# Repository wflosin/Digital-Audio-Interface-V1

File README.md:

This is a complete design for a digital audio interface. The features include:
- 1/4" jack input (mono)
- Headphone output (loobpack or computer audio output)
- Active tone control, three knobs (bass, mid, treble) 
- Active volume control
- Clipping indicator
- HID buttons (mute, volume up, volume down)
- Entirely USB-powered
- No screws needed, the panel snap fits into the enclosure

What is found in this repository:
- Schematic and Board files (Eagle CAD)
- Images of the schematic and board
- Parts list, and Digikey order
- Gerber files
- 3D models for the enclosure, and potentiometer and button caps

The circuit uses the audio codex PCM2906 from TI, which includes a USB interface. Although many of the parts can be hand-soldered, it is recoommended to reflow solder the board. 

The overall cost of parts and printing was approximately $115 CAD (Oct-2025). Parts were selected to minimize noise thorughout the circuit, and so cheaper alternatives could be used instead. 
Parts were ordered through Digikey and from Texas Instruments. The enclosure was 3D printed, but a metal enclosure could probe useful for shielding. 

Notable issues to be improved on in the next iteration: 
- Headphone pop when plugging in
- When the bass tone control is turned up too high, all sound cuts out
- When listening through headphones on the loobback setting, the only way to control the headphone volume is with the gain knob. This should have a separate volume control. 

Noise and performance metrics of the board were not evaluated once completed. Audio quality was sufficient for this iteration, but naturally, performance metrics are a must potentially commercializable devices. 

I hope you like it!

Below are several sources that helped in the creation of this design:
- https://www.theseus.fi/bitstream/handle/10024/857714/Heikkinen_Tuomas-Pyry.pdf
- https://kastner.ucsd.edu/ryan/wp-content/uploads/sites/5/2022/06/admin/usb-audio-interface.pdf
- https://guitarnuts2.proboards.com/thread/7842/modeling-electric-guitar-ltspice
- https://circuitdigest.com/electronic-circuits/audio-equalizer-tone-control-circuit-with-bass-treble-and-mid-frequency-control
- https://www.ti.com/lit/ug/tidu034/tidu034.pdf
- Small Signal Audio Design, by Douglas Self (chapter 9)
- https://www.edn.com/signal-distortion-from-high-k-ceramic-capacitors/

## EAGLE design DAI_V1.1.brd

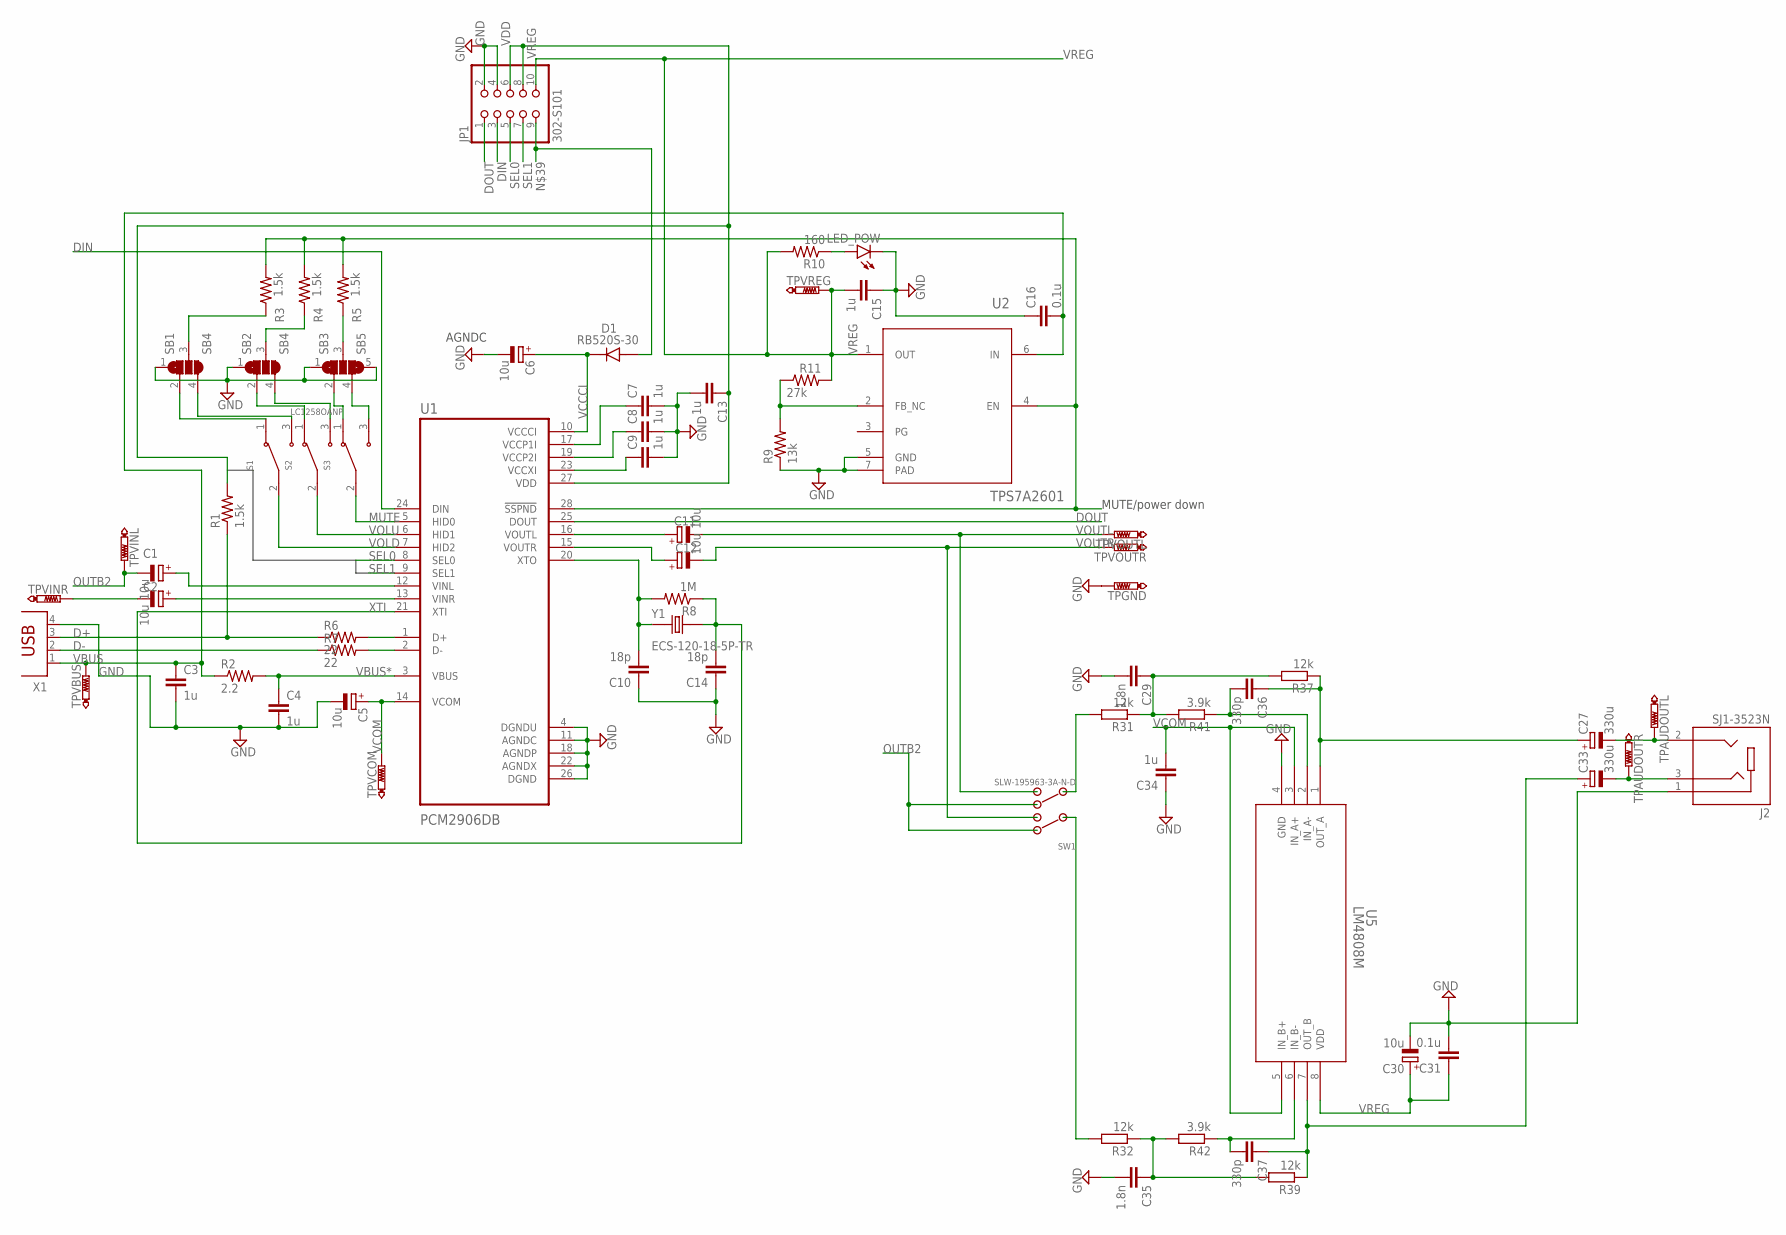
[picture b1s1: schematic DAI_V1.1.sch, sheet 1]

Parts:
C1, C2, C11, C12: 10u; PANASONIC_D
C3, C4, C7, C8, C9, C13, C15, C34: 1u; C0805
C5, C6, C30: 10u; PANASONIC_B
C10, C14: 18p; C0805
C16, C31: 0.1u; C0805
C27, C33: 330u; E3,5-10
C29, C35: 1.8n; C1206
C36, C37: 330p; C1206
D1: RB520S-30; DIO_RB520S-30
J2: SJ1-3523N; CUI_SJ1-3523N
JP1: 302-S101; 2X05
LED_POW: LED5MM
R1, R3, R4, R5: 1.5k; R0805
R2: 2.2; R0805
R6, R7: 22; R0805
R8: 1M; R0805
R9: 13k; R0805
R10: 160; R0805
R11: 27k; R0805
R31, R32, R37, R39: 12k; M1206
R41, R42: 3.9k; M1206
S1, S3: LC1258EENP; SW_LC1258EENP
S2: LC1258OANP; SW_LC1258EENP
SB1, SB2: SB4
SB3: SB5
SW1: SLW-195963-3A-N-D; SW-T3-4B-A-A3-S2
TPAUDOUTL: PTR1PAD1-13; P1-13
TPAUDOUTR: PTR1PAD1-13; P1-13
TPGND: PTR1PAD1-13; P1-13
TPVBUS: PTR1PAD1-13; P1-13
TPVCOM: PTR1PAD1-13; P1-13
TPVINL: PTR1PAD1-13; P1-13
TPVINR: PTR1PAD1-13; P1-13
TPVOUTL: PTR1PAD1-13; P1-13
TPVOUTR: PTR1PAD1-13; P1-13
TPVREG: PTR1PAD1-13; P1-13
U1: PCM2906DB; SOP65P780X200-28N
U2: TPS7A2601; DRV0006A_NV
U5: LM4808M; M08A
X1: PN61729
Y1: ECS-120-18-5P-TR; XTAL_ECS-120-18-5P-TR

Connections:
AUDOUTL: C27.-, J2.2, TPAUDOUTL.TP
AUDOUTR: C33.-, J2.3, TPAUDOUTR.TP
D+: R1.1, R6.1, X1.3
D-: R7.1, X1.2
DIN: JP1.3, U1.24 (DIN)
DOUT: JP1.1, U1.25 (DOUT)
GND: C3.2, C4.2, C5.-, C6.-, C7.2, C8.2, C9.2, C10.1, C13.2, C14.1, C15.1, C16.1, C29.2, C30.-, C31.2, C34.1, C35.2, J2.1, JP1.2, JP1.4, LED_POW.K (C), R9.1, SB1.1, SB2.1, SB3.1, SB3.5, TPGND.TP, U1.4 (DGNDU), U1.11 (AGNDC), U1.18 (AGNDP), U1.22 (AGNDX), U1.26 (DGND), U2.5 (GND), U2.7 (PAD), U5.4 (GND), X1.4; also elsewhere on the board
MUTE: S3.2 (COM), U1.5 (HID0)
unnamed: R6.2, U1.1 (D+)
unnamed: R7.2, U1.2 (D-)
unnamed: R32.2, SW1.2
unnamed: R3.1, SB1.3
unnamed: C29.1, R31.1, R37.2, R41.2
unnamed: R5.1, SB3.3
unnamed: LED_POW.A, R10.1
unnamed: C35.1, R32.1, R39.2, R42.2
unnamed: C33.+, C37.1, R39.1, U5.7 (OUT_B)
unnamed: R4.1, SB2.3
unnamed: S1.1 (NC), SB1.2
unnamed: R9.2, R11.1, U2.2 (FB_NC)
unnamed: C11.+, U1.16 (VOUTL)
unnamed: C12.+, U1.15 (VOUTR)
unnamed: S1.3 (NO), SB1.4
unnamed: S2.1 (NC), SB2.2
unnamed: S2.3 (NO), SB2.4
unnamed: S3.1 (NC), SB3.2
unnamed: S3.3 (NO), SB3.4
unnamed: C36.2, R41.1, U5.2 (IN_A-)
unnamed: R31.2, SW1.5
unnamed: C27.+, C36.1, R37.1, U5.1 (OUT_A)
unnamed: D1.A, JP1.9
unnamed: C37.2, R42.1, U5.6 (IN_B-)
OUTB2: C1.-, SW1.1, SW1.4, TPVINL.TP; also elsewhere on the board
SEL0: JP1.5, U1.8 (SEL0)
SEL1: JP1.7, U1.9 (SEL1)
SSPND: R3.2, R4.2, R5.2, U1.28 (!SSPND), U2.4 (EN)
VBUS: C3.1, C16.2, R2.1, TPVBUS.TP, U2.6 (IN), X1.1
VBUS*: C4.1, R2.2, U1.3 (VBUS)
VCCCI: C6.+, D1.C (K), U1.10 (VCCCI)
VCCP1I: C7.1, U1.17 (VCCP1I)
VCCP2I: C8.1, U1.19 (VCCP2I)
VCCXI: C9.1, U1.23 (VCCXI)
VCOM: C5.+, C34.2, TPVCOM.TP, U1.14 (VCOM), U5.3 (IN_A+), U5.5 (IN_B+); also elsewhere on the board
VDD: C13.1, JP1.6, JP1.8, R1.2, U1.27 (VDD)
VINL: C1.+, U1.12 (VINL)
VINR: C2.-, TPVINR.TP
VINR*: C2.+, U1.13 (VINR)
VOLD: S1.2 (COM), U1.7 (HID2)
VOLU: S2.2 (COM), U1.6 (HID1)
VOUTL: C11.-, SW1.6, TPVOUTL.TP
VOUTR: C12.-, SW1.3, TPVOUTR.TP
VREG: C15.2, C30.+, C31.1, JP1.10, R10.2, R11.2, TPVREG.TP, U2.1 (OUT), U5.8 (VDD); also elsewhere on the board
XTI: C14.2, R8.1, U1.21 (XTI), Y1.2
XTO: C10.2, R8.2, U1.20 (XTO), Y1.1

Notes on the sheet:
MUTE/power down
AGNDC

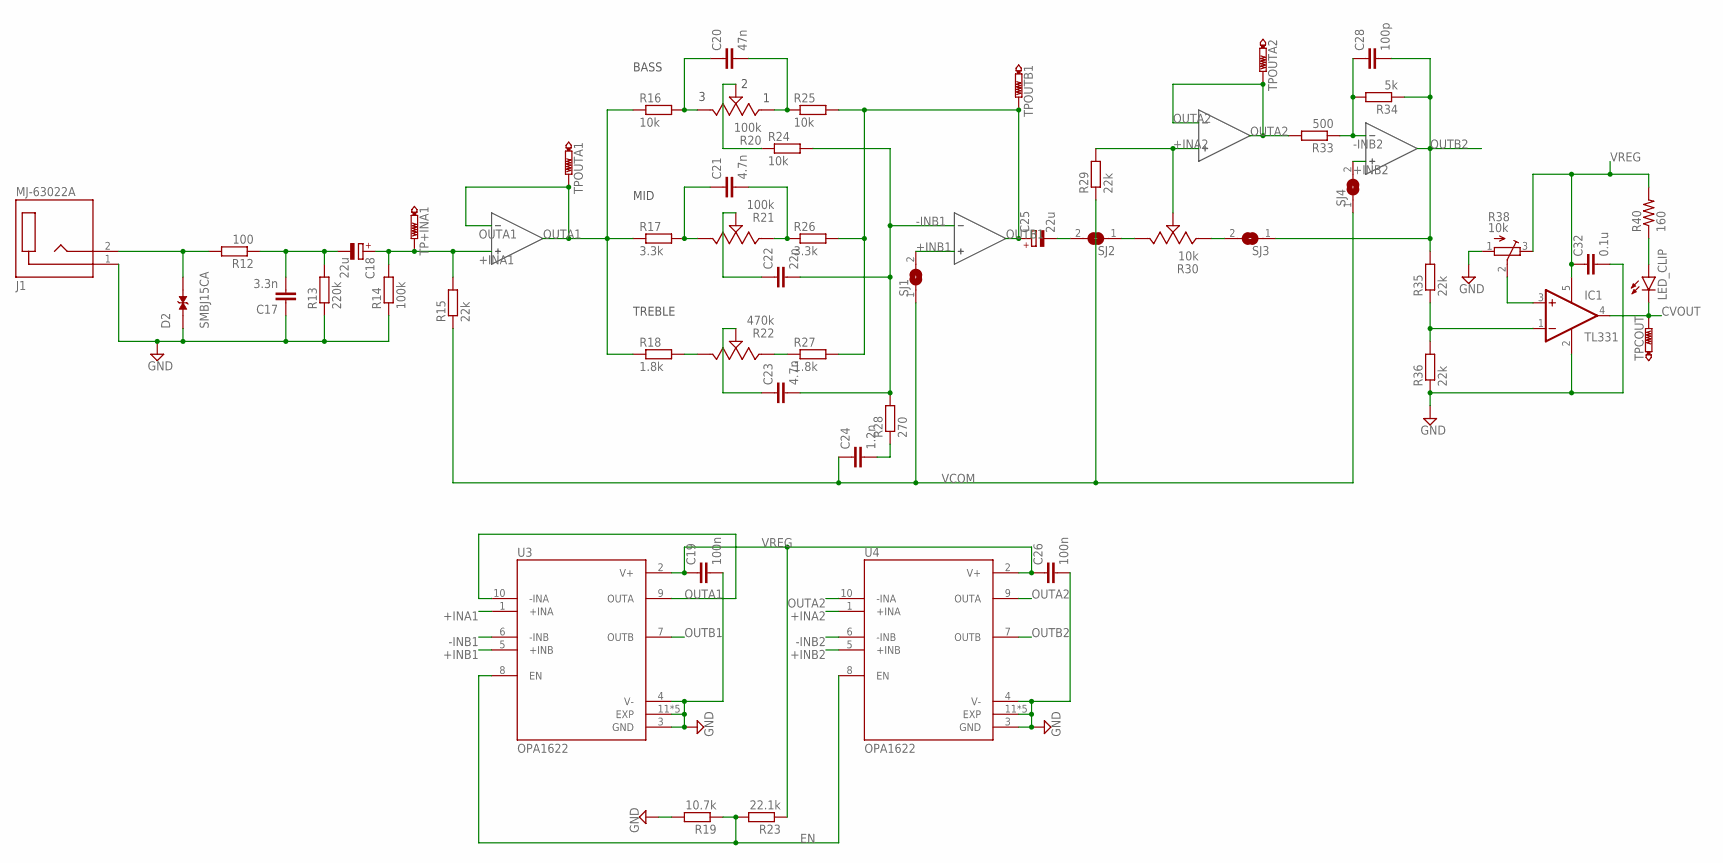
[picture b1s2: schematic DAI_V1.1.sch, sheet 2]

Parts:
C17: 3.3n; C1206
C18, C25: 22u; PANASONIC_D
C19, C26: 100n; C0805
C20: 47n; C1206
C21, C23: 4.7n; C1206
C22: 22n; C1206
C24: 1.2n; C1206
C28: 100p; C1206
C32: 0.1u; C0805
D2: SMBJ15CA; DIOM4336X265N
IC1: TL331; DBV-R-PDSO-G5
J1: MJ-63022A; CUI_MJ-63022A
LED_CLIP: LED5MM
R12: 100; M1206
R13: 220k; M1206
R14: 100k; M1206
R15, R29, R35, R36: 22k; M1206
R16, R24, R25: 10k; M1206
R17, R26: 3.3k; M1206
R18, R27: 1.8k; M1206
R19: 10.7k; R1206
R20, R21: 100k; POT_PTN16-A100125K1B1
R22: 470k; POT_PTN16-A100125K1B1
R23: 22.1k; R1206
R28: 270; M1206
R30: 10k; POT_PTN16-A100125K1B1
R33: 500; M1206
R34: 5k; M1206
R38: 10k; 601030_AVX
R40: 160; R0805
SJ1, SJ2, SJ3, SJ4: SJW
TP+INA1: PTR1PAD1-13; P1-13
TPCOUT: PTR1PAD1-13; P1-13
TPOUTA1, TPOUTA2: PTR1PAD1-13; P1-13
TPOUTB1: PTR1PAD1-13; P1-13
U3, U4: OPA1622; IC_OPA1622IDRCR

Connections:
+INA1: C18.+, R14.2, R15.2, TP+INA1.TP, U3.1 (+INA)
+INA2: R29.2, R30.2, U4.1 (+INA)
+INB1: SJ1.2, U3.5 (+INB)
+INB2: SJ4.2, U4.5 (+INB)
-INB1: C22.2, C23.2, R24.2, R28.2, U3.6 (-INB)
-INB2: C28.1, R33.1, R34.2, U4.6 (-INB)
CVOUT: IC1.4 (OUT), LED_CLIP.K (C), TPCOUT.TP
EN: R19.1, R23.2, U3.8 (EN), U4.8 (EN)
GND: C17.1, C19.2, C26.2, C32.2, D2.1, IC1.2 (GND), J1.1 (SLEEVE), R13.1, R14.1, R19.2, R36.1, R38.1 (A), U3.3 (GND), U3.4 (V-), U3.11 (EXP), U3.12 (EXP), U3.13 (EXP), U3.14 (EXP), U3.15 (EXP), U4.3 (GND), U4.4 (V-), U4.11 (EXP), U4.12 (EXP), U4.13 (EXP), U4.14 (EXP), U4.15 (EXP); also elsewhere on the board
unnamed: R18.2, R22.3
unnamed: R22.1, R27.1
unnamed: C25.-, SJ2.2
unnamed: D2.2, J1.2 (TIP), R12.2
unnamed: C17.2, C18.-, R12.1, R13.2
unnamed: C21.1, R17.2, R21.3
unnamed: C21.2, R21.1, R26.1
unnamed: R30.3, SJ2.1
unnamed: C20.1, R16.2, R20.3
unnamed: IC1.1 (-IN), R35.1, R36.2
unnamed: C20.2, R20.1, R25.1
unnamed: R20.2, R24.1
unnamed: R30.1, SJ3.2
unnamed: C23.1, R22.2
unnamed: C22.1, R21.2
unnamed: IC1.3 (+IN), R38.2 (S)
unnamed: LED_CLIP.A, R40.1
unnamed: C24.2, R28.1
OUTA1: R16.1, R17.1, R18.1, TPOUTA1.TP, U3.9 (OUTA), U3.10 (-INA)
OUTA2: R33.2, TPOUTA2.TP, U4.9 (OUTA), U4.10 (-INA)
OUTB1: C25.+, R25.2, R26.2, R27.2, TPOUTB1.TP, U3.7 (OUTB)
OUTB2: C28.2, R34.1, R35.2, SJ3.1, U4.7 (OUTB); also elsewhere on the board
VCOM: C24.1, R15.1, R29.1, SJ1.1, SJ4.1; also elsewhere on the board
VREG: C19.1, C26.1, C32.1, IC1.5 (V+), R23.1, R38.3 (E), R40.2, U3.2 (V+), U4.2 (V+); also elsewhere on the board

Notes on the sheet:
BASS
MID
TREBLE

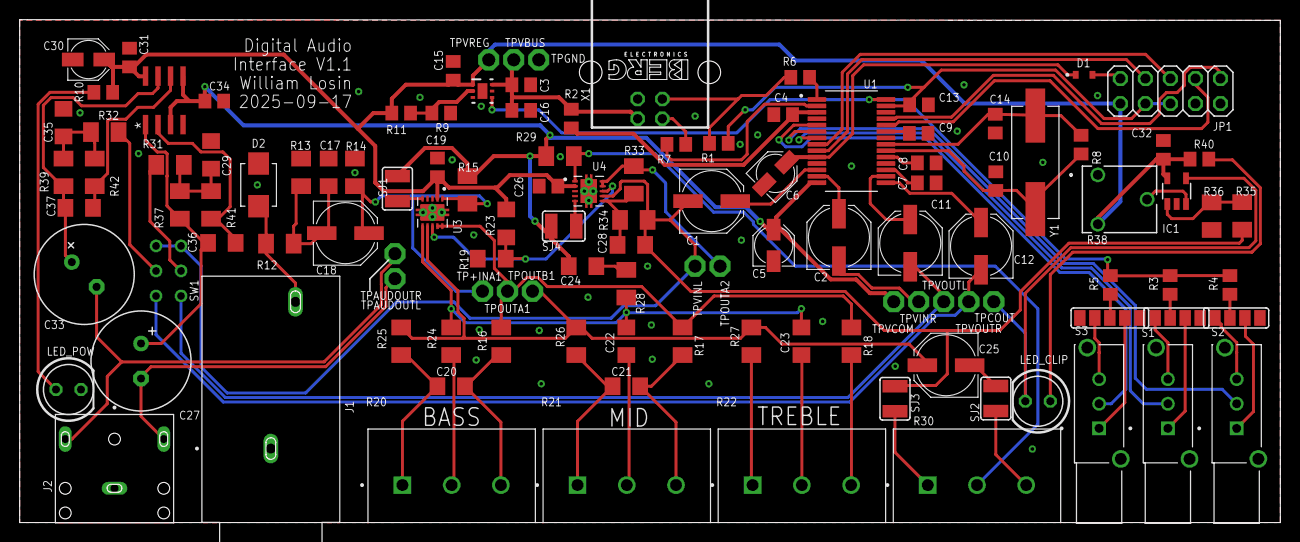
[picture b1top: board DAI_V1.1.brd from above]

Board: 2 copper layers, 128.0 x 51.1 mm, 120 parts (0 on the bottom side), 83 nets.

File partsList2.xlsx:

Partlist
Exported from DAI_V1.brd at 2025-09-17 1:20 AM
 |  |  | Components on audio path
EAGLE Version 9.6.2 Copyright (c) 1988-2020 Autodesk, Inc. |  |  | Page 2
 |  |  | Page 1
Assembly variant:
 |  |  |  |  |  |  | 40.524000000000001
 |  |  |  |  |  |  | 68.784000000000006
Part | Value | Device | Description | Price per unit | Required quantity | Tentative quantity | Total Cost | Aquired | Link
R2 | 2.2000000000000002 | RES 2.2 OHM 1% 1/4W 0805 | VBUS | 0.16 | 1 | 1 | 0.16
R6, R7 | 22 | RES 22 OHM 1% 1/4W 0805 | USB data | 0.16 | 2 | 2 | 0.32
R12 | 100 | RES 100 OHM 1% 1/4W 1206 | RF Filter | 0.16 | 1 | 1 | 0.16
R10, R40 | 160 | RES 160 OHM 1% 1/4W 0805 | LED Resistors | 0.16 | 2 | 2 | 0.32
R28 | 270 | RES SMD 270 OHM 1% 1/4W 1206 | Tone EQ | 0.16 | 1 | 1 | 0.16
R33 | 510 | RES SMD 510 OHM 1% 1/4W 1206 | Baxandall | 0.16 | 1 | 1 | 0.16
C16, C19, C26, C31, C32 | 0.1u | CAP CER 0.1UF 50V X7R 0805 | Bypass caps | 1.2999999999999999E-2 | 5 | 10 | 0.13
C24 | 1.2n | CAP CER 1200PF 50V C0G/NPO 1206 | Tone EQ | 0.66 | 1 | 1 | 0.66
R1, R3, R4, R5 | 1.5k | RES 1.5K OHM 1% 1/4W 0805 | Pullup? | 0.16 | 4 | 4 | 0.64
R18, R27 | 1.8k | RES 1.8K OHM 1% 1/4W 1206 | Treble | 0.16 | 2 | 2 | 0.32
C29, C35 | 1.8n | CAP CER 1800PF 50V C0G/NPO 1206 | Headphone caps, C0G | 0.5 | 2 | 2 | 1
R19 | 10.7k | RES 10.7K OHM 1% 1/4W 1206 | EN stabilizer | 0.16 | 1 | 1 | 0.16
R14 | 100k | RES 100K OHM 1% 1/4W 1206 | RF Filter | 0.16 | 1 | 1 | 0.16
R20, R21 | 100k | POT_PTN16-A100125K1B1 | rotary potentiometer | 1.76 | 2 | 2 | 3.52
C28 | 100p | CAP CERAMIC 100PF 1KV C0G NP0 | Baxandall | 0.19 | 1 | 1 | 0.19
R16, R24, R25 | 10k | RES 10K OHM 1% 1/4W 1206 | Bass | 0.16 | 3 | 3 | 0.48
R30 | 10k | POT_PDB181-K425K-103B | rotary potentiometer | 1.89 | 1 | 1 | 1.89
R38 | 10k | 601030 | Clipping set point |  | 0 | 0 | 0
C1, C2/C11, C12 | 10u | PANASONIC_D. CAP ALUM 10UF 20% 50V SMD | VINL/R/VOUTL/R coupling caps, bipolar | 0.57999999999999996 | 4 | 4 | 2.3199999999999998
C5, C6, C30 | 10u | PANASONIC_B, CAP ALUM 10UF 20% 25V SMD | Bypass caps | 0.26 | 3 | 3 | 0.78
R31, R32, R37, R39 | 12k | RES 12K OHM 1% 1/4W 1206 | Headphone resistors | 6.0999999999999999E-2 | 4 | 10 | 0.61
R9 | 13k | RES SMD 13K OHM 0.1% 1/4W 0805 | VREG voltage divider | 0.33 | 1 | 1 | 0.33
C10, C14 | 18p | CAP CER 18PF 50V C0G/NPO 0805 | Crystal caps | 0.15 | 2 | 2 | 0.3
R8 | 1M | RES 1M OHM 1% 1/4W 0805 | Crystal resistor | 0.16 | 1 | 1 | 0.16
C3, C4, C7, C8, C9, C13, C15, C34 | 1u | CAP CER 1UF 50V X7R 0805 | Bypass caps/filters | 1.9E-2 | 8 | 10 | 0.19
R23 | 22.1k | RES 22.1K OHM 1% 1/4W 1206 | EN stabilizer | 0.16 | 1 | 1 | 0.16
R13 | 220k | RES 220K OHM 1% 1/4W 1206 | RF Filter | 0.16 | 1 | 1 | 0.16
R15, R29/R35, R36 | 22k | RES 22K OHM 1% 1/4W 1206 | Bias Resistor/comp V divider | 0.16 | 4 | 4 | 0.64
C22 | 22n | CAP CER 0.022UF 100V C0G 1206 | Mid | 0.51 | 1 | 1 | 0.51
C18/C25 | 22u | PANASONIC_D, CAP ALUM 22UF 20% 35V SMD | RF Filter/Interstage coupling, bipolar | 0.6 | 2 | 2 | 1.2
R11 | 27k | RES SMD 27K OHM 0.1% 1/4W 0805 | VREG voltage divider | 0.33 | 1 | 1 | 0.33
R17, R26 | 3.3k | RES SMD 3.3K OHM 1% 1/4W 1206 | Mid | 0.16 | 2 | 2 | 0.32
C17 | 3.3n | CAP CER 3300PF 630V C0G/NP0 1206 | RF Filter | 0.2 | 1 | 1 | 0.2
R41, R42 | 3.9k | RES 3.9K OHM 1% 1/4W 1206 | Headphone resistors | 0.16 | 2 | 2 | 0.32
C36, C37 | 330p | CAP CER 330PF 50V C0G/NP0 1206 | Headphone caps, C0G | 0.22 | 2 | 2 | 0.44
C27, C33 | 330u | E3,5-10 | Headphone coupling cap | 1.1200000000000001 | 2 | 2 | 2.2400000000000002
C21, C23 | 4.7n | CAP CER 4700PF 100V C0G/NP0 1206 | Mid/Treble caps | 0.36 | 2 | 2 | 0.72
C20 | 47n | CAP CER 47000PF 100V C0G 1206 | Bass cap | 0.96 | 1 | 1 | 0.96
R34 | 5.1k | RES SMD 5.1K OHM 1% 1/4W 1206 | Baxandall | 0.16 | 1 | 1 | 0.16
R22 | 500k | POT_PTN16-A500125K1B1 | rotary potentiometer | 1.76 | 1 | 1 | 1.76
Y1 | ECS-120-18-5P-TR | XTAL_ECS-120-18-5P-TR | Crystal for clock | 1.1000000000000001 | 1 | 1 | 1.1000000000000001
S1, S2, S3 | LC1258OANP | SW_LC1258EENP | HID pushbutton | 1.65 | 3 | 3 | 4.9499999999999993
U5 | LM4808M | M08A | Headphone amplifier | 1.24 | 1 | 1 | 1.24
J1 | MJ-63022A | MJ-63022A | 1/4" Jack, mono | 1.85 | 1 | 1 | 1.85
U3, U4 | OPA1622 | IC_OPA1622IDRCR | Audio op amp | 7.0720000000000001 | 2 | 2 | 14.144
U1 | PCM2906DB | SOP65P780X200-28N | TI USB Codec | 12.51 | 1 | 1 | 12.51
D1 | RB520S-30 | DIO_RB520S-30 | VREG Schottky diode | 0.25 | 1 | 1 | 0.25
J2 | SJ1-3523N | CUI_SJ1-3523N | 3.5mm phone jack | 1.21 | 1 | 1 | 1.21
SW1 | SLW-195963-3A-N-D | SW-T3-4B-A-A3-S2 | DPDT Switch | 0.68 | 1 | 1 | 0.68
D2 | SMBJ15CA | DIOM4336X265N | TVS Diode | 0.52 | 1 | 1 | 0.52
IC1 | TL331 | DBV-R-PDSO-G5 | Comparator | 0.67 | 1 | 1 | 0.67
U2 | TPS7A2601 | DRV0006A_NV | TI Voltage regulator | 1.61 | 1 | 1 | 1.61
JP1 |  | 2X05 | Test headers | 0.38 | 1 | 1 | 0.38
LED_CLIP |  | LED5MM | Yellow | 0.4 | 1 | 1 | 0.4
LED_POW |  | LED5MM | Green | 0.33 | 1 | 1 | 0.33
X1 |  | PN61729 | USB | 1.7 | 1 | 1 | 1.7

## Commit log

2025-10-26 Added the LTSpice Simulation File
    This was used to simulate the guitar output and the gain stages, including the tone and volume control circuits.

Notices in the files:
parts and their libraries:
COPYRIGHT: Copyright (C) 2025 Ultra Librarian. All rights reserved.
